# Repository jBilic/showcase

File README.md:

# Showcase
This is a showcase repository for __some of my work__ in field of electronics design.
Majority of my work is related to my private projects and experiments. 
On the professional side, by far the largest and most complex project is one called __Wireless IO__. 
Unfortunately I cannot disclose any details publicly - that's why I've only uploaded photos of final designs.

If you want to know more details, feel free to contact me.

## ESP32
As you might have concluded by now, I do a lot of my projects with ESP32.
Main reason being that majority of my projects are IoT prototypes and I need an MCU with network connectivitiy.
ESP is therefore a perfect candidate with a huge range of SoC's, modules, examples etc.

For quick and dirty projects I use Arduino IDE, but recently I've started to use ESP-IDF.
Projects I've done up to this pooint have involved features like:
* sensor data reading (temperature, humiditiy, pressure, light etc.)
* radio communication 
* Bluetooth
* motion detection
* ESP hosted servers and websites
* LoRa
* light control (LED's)
* power control 
* RTOS
* Power modes

Projects involved were a IoT Coffee Machine, Home Security System, Remote Watering station etc.

## STM32
I haven't done a lot of work on STM products. As part of my professional work I do work with them, but this is mainly debugging, flashing etc.
Recently I've acquired and STM Discovery board but haven't done a lot other than playing with some RTOS scheduling, running examples etc.

LAST UPDATED: December 2021.

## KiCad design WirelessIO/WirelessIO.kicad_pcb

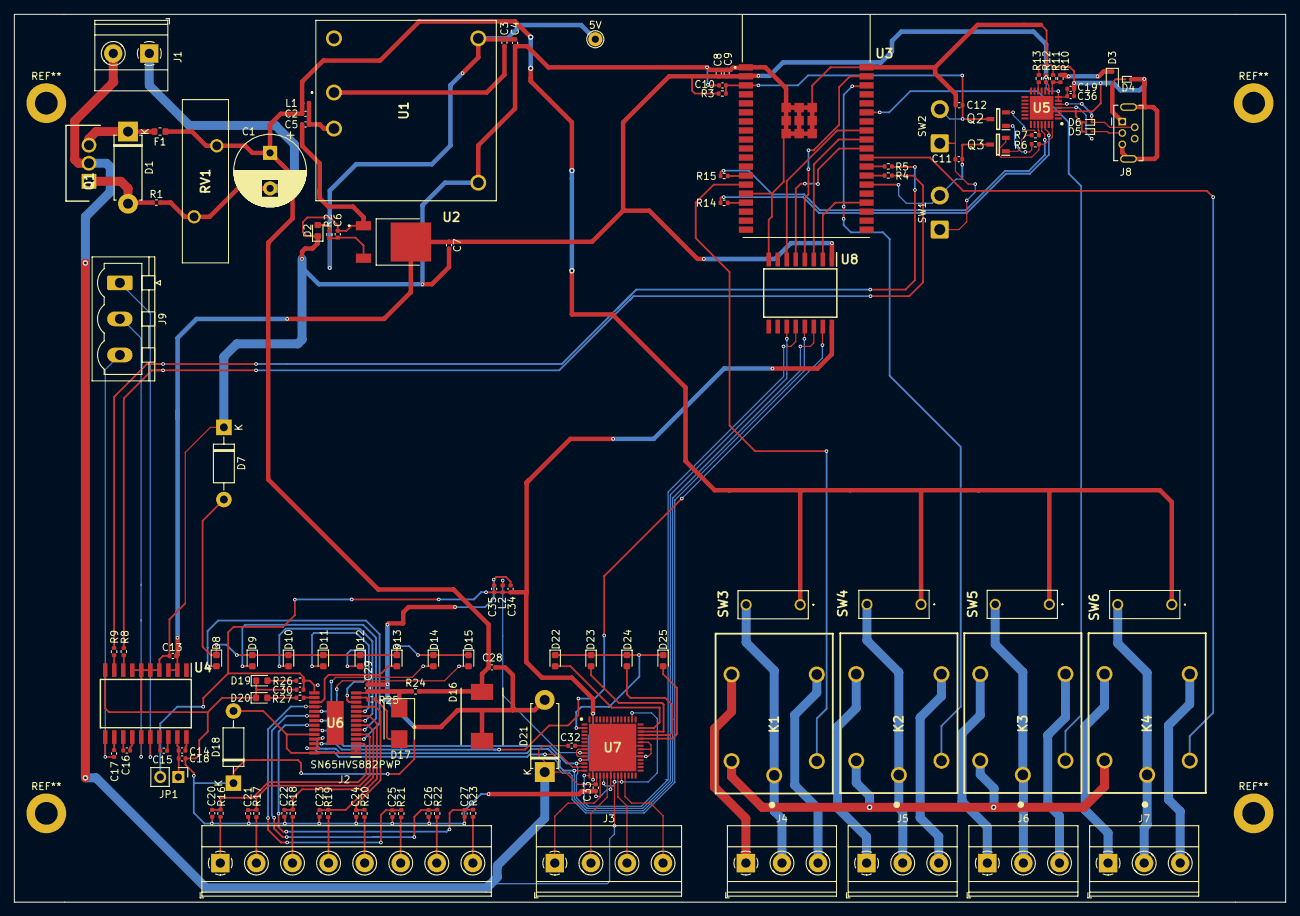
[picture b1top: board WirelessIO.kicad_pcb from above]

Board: 2 copper layers, 179.0 x 125.0 mm, 123 parts (0 on the bottom side), 114 nets.

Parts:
5V: 5V; TestPoint_THTPad_D2.0mm_Drill1.0mm
C1: 330uF/50V; CP_Radial_D10.0mm_P5.00mm
C2: 1uF/50V; C_0402_1005Metric
C3, C5: 1nF/2kV; C_0402_1005Metric
C4, C34: 10uF; C_0402_1005Metric
C6, C7: 22uF/10V; C_0402_1005Metric
C8: 22uF; C_0402_1005Metric
C9, C13, C18: 0.1uF; C_0402_1005Metric
C10, C33: 1uF; C_0402_1005Metric
C11, C12, C36: 0.1uF/50V; C_0402_1005Metric
C14: 0.1uF/10V; C_0402_1005Metric
C15, C16, C17: 0.1uF/16V; C_0402_1005Metric
C19: 4.7uF/6.3V; C_0402_1005Metric
C20, C21, C22, C23, C24, C25, C26, C27: 22nF; C_0402_1005Metric
C28: 4,7uF/2kV; C_0402_1005Metric
C29: 10uF/60V; C_0402_1005Metric
C30: 2.2uF; C_0402_1005Metric
C32: 10uF, 6.3V; C_0402_1005Metric
C35: 100nF; C_0402_1005Metric
D1: 1N5237B; D_5W_P10.16mm_Horizontal
D2, D8, D9, D10, D11, D12, D13, D14, D15, D19, D20, D22, D23, D24, D25: LED; LED_0603_1608Metric
D3: D_Schottky; D_SOD-323
D4, D5, D6: ESD9B5.0ST5G; D_SOD-923
D7, D18: 1N4007; D_DO-41_SOD81_P10.16mm_Horizontal
D16: SM15T39CA; DIONM8059X265N
D17: Z2SMB36; D_SMB
D21: D_Zener; D_5W_P10.16mm_Horizontal
F1: 2A; Fuse_0603_1608Metric
J1: PWR_IN; TerminalBlock_Phoenix_MKDS-1,5-2-5.08_1x02_P5.08mm_Horizont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
J2: SIGNAL_IN; TerminalBlock_Phoenix_MKDS-1,5-8-5.08_1x08_P5.08mm_Horizont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
J3: Screw_Terminal_01x04; TerminalBlock_Phoenix_MKDS-1,5-4-5.08_1x04_P5.08mm_Horizont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
J4: Relay_1; TerminalBlock_Phoenix_MKDS-1,5-3-5.08_1x03_P5.08mm_Horizont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
J5: Relay_2; TerminalBlock_Phoenix_MKDS-1,5-3-5.08_1x03_P5.08mm_Horizont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
J6: Relay_3; TerminalBlock_Phoenix_MKDS-1,5-3-5.08_1x03_P5.08mm_Horizont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
J7: Relay_4; TerminalBlock_Phoenix_MKDS-1,5-3-5.08_1x03_P5.08mm_Horizont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
J8: USB_B_Mini; USB_Mini-B_Tensility_54-00023_Vertical
J9: Conn_01x03; PhoenixContact_MSTBVA_2,5_3-G-5,08_1x03_P5.08mm_Vertical
JP1: Jumper; PinHeader_1x02_P2.54mm_Vertical
K1, K2, K3, K4: G5LE-1-DC5; G5LE-1
L1: 4.7uH; L_0402_1005Metric
L2: 100uH; L_0402_1005Metric
Q1: FQP47P06; TO254P483X1016X2261-3P
Q2, Q3: SS8050-G; SOT95P240X115-3N
R1: 100k; R_0402_1005Metric
R2: 2k(5%); R_0402_1005Metric
R3, R13: 10k; R_0402_1005Metric
R4, R5: 0R; R_0402_1005Metric
R6, R7: 10k(5%); R_0402_1005Metric
R8, R9, R14, R15: 0R(5%); R_0402_1005Metric
R10: 22.1k; R_0402_1005Metric
R11: 47.5k; R_0402_1005Metric
R12: 2k; R_0402_1005Metric
R16, R17, R18, R19, R20, R21, R22, R23: 1.2k; R_0402_1005Metric
R24: 56R; R_0402_1005Metric
R25: 24.9k; R_0402_1005Metric
R26, R27: 1.3k; R_0402_1005Metric
RV1: B72220S1300K102
SW1, SW2: SW_Push; SolderWire-0.75sqmm_1x02_P4.8mm_D1.25mm_OD2.3mm
SW3, SW4, SW5, SW6: SW_DIP_x01; DS01254L01BE
U1: PDQE10-Q24-S5-D; PDQE10Q24S5D
U2: LM1117IDTX-3.3_NOPB; LM1117IDTX33NOPB
U3: ESP32-WROVER-IE_M213EH3264UH3Q0_; ESP32WROVERIEM213EH3264UH3Q0
U4: ADM3251EARWZ; SOIC127P1032X265-20N
U5: CP2102N-A02-GQFN28; QFN50P500X500X80-29N-D
U6: SN65HVS882PWP; SOP65P640X120-29N
U7: MAX14913AKN+T; QFN50P800X800X90-57N
U8: ISO7762DW; SOIC127P1030X265-16N

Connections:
3V3: C7.1, C8.1, C9.1, C13.1, C19.1, C36.1, R3.1, R12.2, U2.2, U3.2, U4.2, U4.3, U5.6, U5.7, U8.1
5V: 5V.1, C3.2, C4.1, C6.1, R2.1, U1.5, U2.3
5V_ISO: C30.1, C34.1, C35.1, JP1.2, L2.1, R26.1, U6.15, U7.11, U7.16, U7.33, U7.35, U7.37, U7.55, U8.16
/CS1_I: U7.15, U8.12
/EN: C10.1, C12.1, Q2.3, R3.2, SW2.2, U3.3
/GND_ISO: C17.2, J9.3, U4.11
/IN_1: J2.1, R16.1
/IN_2: J2.2, R17.1
/IN_3: J2.3, R18.1
/IN_4: J2.4, R19.1
/IN_5: J2.5, R20.1
/IN_6: J2.6, R21.1
/IN_7: J2.7, R22.1
/IN_8: J2.8, R23.1
/IO0: C11.1, Q3.3, SW1.2, U3.25
/IP0: C20.1, R16.2, U6.3
/IP1: C21.1, R17.2, U6.5
/IP2: C22.1, R18.2, U6.7
/IP3: C23.1, R19.2, U6.9
/IP4: C24.1, R20.2, U6.11
/IP5: C25.1, R21.2, U6.18
/IP6: C26.1, R22.2, U6.20
/IP7: C27.1, R23.2, U6.22
/LED0: D8.2, U6.4
/LED1: D9.2, U6.6
/LED2: D10.2, U6.8
/LED3: D11.2, U6.10
/LED4: D12.2, U6.12
/LED5: D13.2, U6.17
/LED6: D14.2, U6.19
/LED7: D15.2, U6.21
/LEDLS_1_4: D22.1, D23.1, D24.1, D25.1, U7.2
/LX: L2.2, U7.9
/MOSI: U3.37, U8.4
/NC1: J4.1, K1.4
/NC2: J5.1, K2.4
/NC3: J6.1, K3.4
/NC4: J7.1, K4.4
/NO1: J4.3, K1.3
/NO2: J5.3, K2.3
/NO3: J6.3, K3.3
/NO4: J7.3, K4.3
/OUT_1: J3.1, U7.18
/OUT_2: J3.2, U7.20
/OUT_3: J3.3, U7.23
/OUT_4: J3.4, U7.25
/RS232_IN: J9.2, U4.15
/RS232_OUT: J9.1, U4.16
/USB_DN: D6.1, J8.2, U5.5
/USB_DP: D5.1, J8.3, U5.4
/VBUS: D3.1, R10.1
CLK: U3.30, U8.3
CLK_I: U6.25, U7.14, U8.14
CS0: U3.23, U8.2
CS0_I: U6.26, U8.15
CS1: U3.29, U8.5
DTR: Q3.2, R6.2, U5.28
GND: C1.2, J1.1, R1.2, RV1.2
GND1: C4.2, C5.1, C6.2, C7.2, C8.2, C9.2, C10.2, C11.2, C12.2, C13.2, C18.1, C19.2, C20.2, C21.2, C22.2, C23.2, C24.2, C25.2, C26.2, C27.2, C28.1, C29.2, C30.2, C33.2, C34.2, C35.2, C36.2, D2.1, D4.2, D5.2, D6.2, D7.1, D16.1, D17.2, D18.1, D19.1, D20.1, D21.2, J8.5, J8.6, R11.2, R13.2, R25.2, SW1.1, SW2.1, U1.3, U2.1, U3.1, U3.15, U3.38, U3.39, U3.40, U3.41, U3.42, U3.43, U3.44, U3.45, U3.46, U3.47, U4.4, U4.5, U4.6, U4.7, U4.10, U5.3, U5.29, U7.8, U7.10, U7.21, U7.36, U7.50, U8.8, U8.9
GND3: K1.5, K2.5, K3.5, K4.5
MISO: U3.31, U8.6
MISO_I: U6.23, U7.12, U8.11
MOSI_I: U6.27, U7.13, U8.13
unnamed: C2.2, C5.2, L1.2, U1.2
unnamed: C3.1, U1.1
unnamed: C14.1, U4.20
unnamed: C14.2, C18.2, JP1.1, U4.19
unnamed: C15.1, U4.18
unnamed: C15.2, U4.17
unnamed: C16.1, U4.14
unnamed: C16.2, U4.13
unnamed: C17.1, U4.12
unnamed: C29.1, D17.1, R24.1, U6.14
unnamed: C32.2, U7.7
unnamed: D1.1, F1.2, Q1.3
unnamed: D1.2, Q1.1, R1.1
unnamed: D2.2, R2.2
unnamed: D3.2, D4.1, J8.1
unnamed: D7.2, D8.1, D9.1, D10.1, D11.1, D12.1, D13.1, D14.1, D15.1
unnamed: D18.2, U6.1, U6.2, U6.24, U6.28
unnamed: D19.2, R26.2
unnamed: D20.2, R27.2
unnamed: D22.2, U7.41
unnamed: D23.2, U7.40
unnamed: D24.2, U7.39
unnamed: D25.2, U7.38
unnamed: J4.2, K1.1, SW3.2
unnamed: J5.2, K2.1, SW4.2
unnamed: J6.2, K3.1, SW5.2
unnamed: J7.2, K4.1, SW6.2
unnamed: Q2.1, R6.1
unnamed: Q3.1, R7.1
unnamed: R4.2, U3.26
unnamed: R5.2, U3.27
unnamed: R8.1, U4.8
unnamed: R9.1, U4.9
unnamed: R10.2, R11.1, U5.8
unnamed: R12.1, U5.9
unnamed: R13.1, U5.12
unnamed: R14.2, U5.26
unnamed: R15.2, U5.25
unnamed: R25.1, U6.13
unnamed: R27.1, U6.16
PWR_IN: C32.1, C33.1, D21.1, J1.2, Q1.2, U7.17, U7.19, U7.22, U7.24, U7.44
REL_1: K1.2, U3.14
REL_2: K2.2, U3.36
REL_3: K3.2, U3.33
REL_4: K4.2, U3.28
RTS: Q2.2, R7.2, U5.24
RxOUT1: R15.1, U3.13
RxOUT2: R4.1, R8.2
TxIN1: R14.1, U3.16
TxIN2: R5.1, R9.2
VCC: C1.1, C2.1, C28.2, D16.2, F1.1, L1.1, R24.2, RV1.1, SW3.1, SW4.1, SW5.1, SW6.1

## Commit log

2021-07-07 Wireless IO being done as part of my master thesis
